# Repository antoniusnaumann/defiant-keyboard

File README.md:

# Defiant Keyboard
## Firmware
You can find the firmware here: https://github.com/antoniusnaumann/defiant-zmk

## Bill of Materials
(Diodes are not included, order PCBs with diodes assembled)

| Component      | Product                      | Quantity | Link                                                            |
|----------------|------------------------------|----------|-----------------------------------------------------------------|
| Hotswap Socket | Gateron KS-33 Hotswap Socket | 44       | https://www.aliexpress.com/item/1005006042596309.html           |
| LiPo Battery   | LP401230, 3,7V, ~100mAh      |  2       | https://eckstein-shop.de/LiPo-Akku-Lithium-Ion-Polymer-Batterie-37V-105mAh-mit-JST-PHR-2-Stecker-LP401230 |
| Connector      | JST-PH 2.0 2 Pin Angled      |  2       | https://www.digikey.de/de/products/detail/jst-sales-america-inc/S2B-PH-K-S/926626 | 
| Controller     | Seeedstudio XIAO nrf52840    |  2       | https://www.seeedstudio.com/Seeed-XIAO-BLE-nRF52840-p-5201.html | 
| EVA Foam*      | 2mm and 1mm                  |  1 each  | |

*EVA foam is optional and needs to be cut with a laser cutter. See SVG files in case/

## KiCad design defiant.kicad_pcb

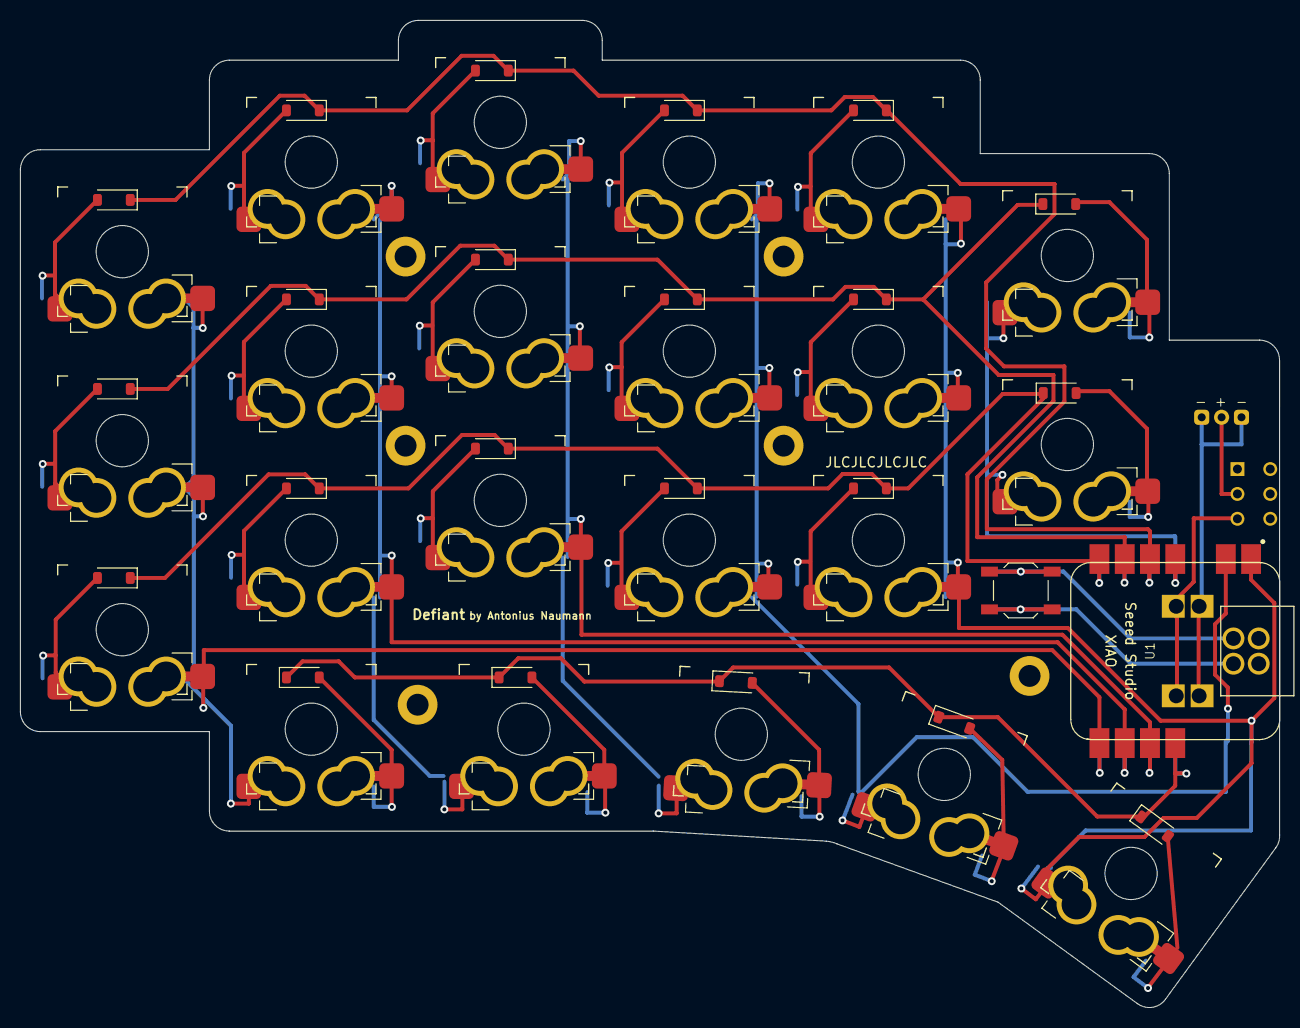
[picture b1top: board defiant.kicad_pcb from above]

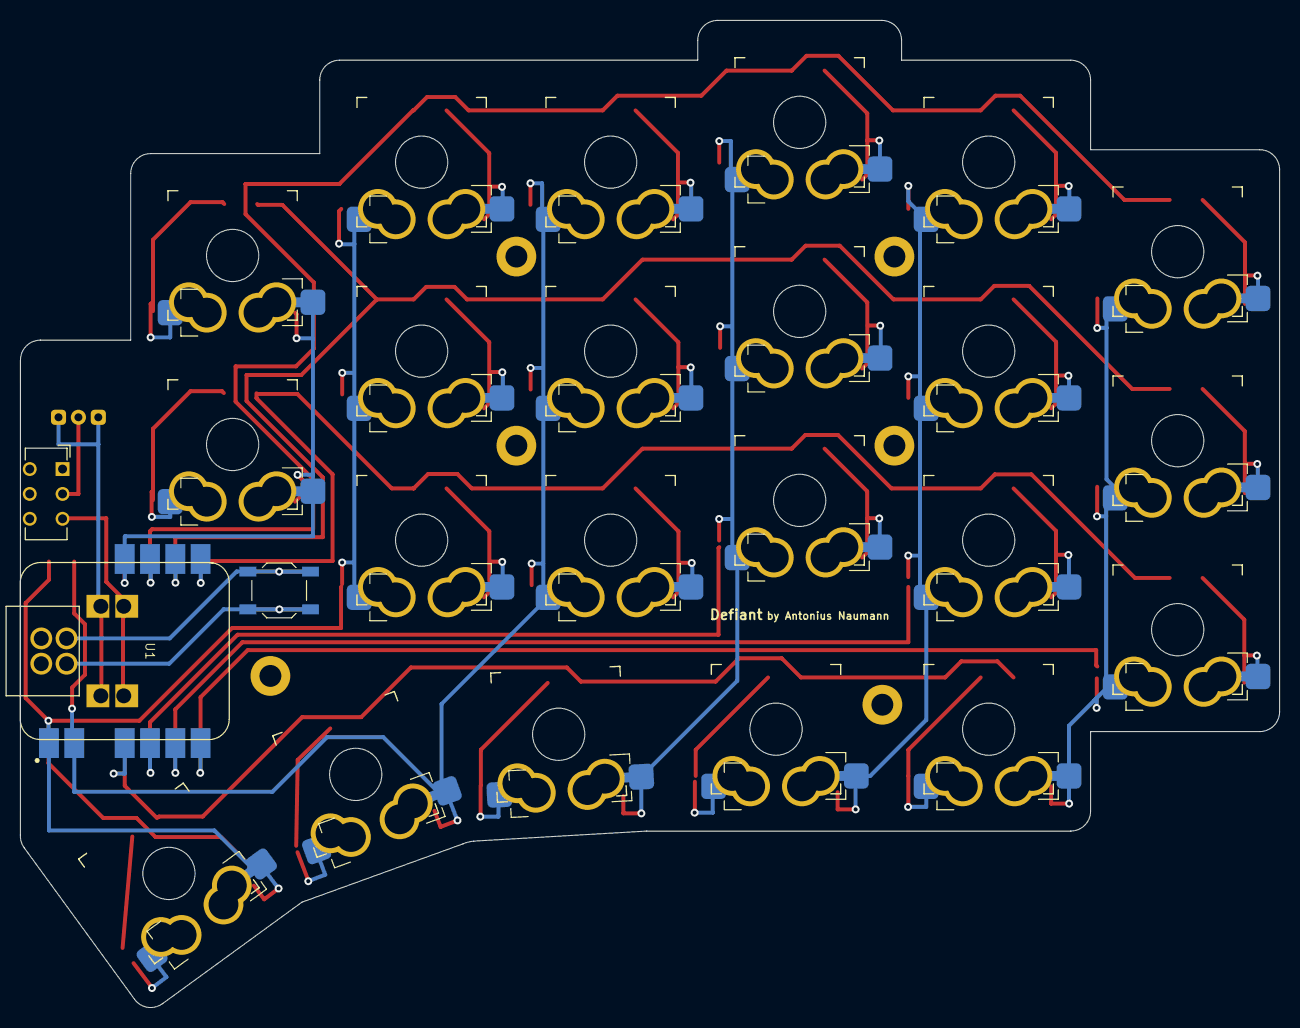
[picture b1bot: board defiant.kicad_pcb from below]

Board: 2 copper layers, 126.6 x 99.2 mm, 49 parts (17 on the bottom side), 37 nets.

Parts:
C0R1, C0R2, C0R3, C1R1, C1R2, C1R3, C2R1, C2R2, C2R3, C3R1, C3R2, C3R3, C4R1, C4R2, C4R3, C5R2, C5R3: SW_PUSH; SW_Gateron_LowProfile_HotSwap_PTH_Reversible
D1, D2, D3, D4, D5, D6, D7, D8, D9, D10, D11, D12, D13, D14, D15, D16, D17, D18, D19, D20, D22, D23: D; D_SOD-123
J1: Conn_01x02_Pin; Lipo Connector
SW1, SW2: SW_Push; SW_SPST_TL3342
SW3: SW_DP3T; SW_CuK_JS202011AQN_DPDT_Angled
T0, T1, T2, T3, T4: SW_PUSH; SW_Gateron_LowProfile_HotSwap_PTH_Reversible
U1: Seeed Studio XIAO BLE; XIAO-nRF52840-Sense-14P-2.54-21X17.8MM_Reduced_Pins

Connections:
unnamed: C0R1.2, D1.2 (A)
unnamed: C0R2.2, D2.2 (A)
unnamed: C0R3.2, D3.2 (A)
unnamed: D4.2 (A), T0.2
unnamed: C1R1.2, D5.2 (A)
unnamed: C1R2.2, D6.2 (A)
unnamed: C1R3.2, D7.2 (A)
unnamed: D8.2 (A), T1.2
unnamed: C2R1.2, D9.2 (A)
unnamed: C2R2.2, D10.2 (A)
unnamed: C2R3.2, D11.2 (A)
unnamed: D12.2 (A), T2.2
unnamed: C3R1.2, D13.2 (A)
unnamed: C3R2.2, D14.2 (A)
unnamed: C3R3.2, D15.2 (A)
unnamed: D16.2 (A), T3.2
unnamed: C4R1.2, D17.2 (A)
unnamed: C4R2.2, D18.2 (A)
unnamed: C4R3.2, D19.2 (A)
unnamed: D20.2 (A), T4.2
unnamed: C5R2.2, D22.2 (A)
unnamed: C5R3.2, D23.2 (A)
unnamed: J1.1, U1.21 (BAT-)
unnamed: J1.2, SW3.2
unnamed: SW1.2, SW2.2, U1.20 (GND)
unnamed: SW3.3, U1.22 (BAT+)
unnamed: SW1.1, SW2.1, U1.19 (RESET)
col0: C0R1.1, C0R2.1, C0R3.1, T0.1, U1.8 (PB09_A7_D7_RX)
col1: C1R1.1, C1R2.1, C1R3.1, T1.1, U1.9 (PA7_A8_D8_SCK)
col2: C2R1.1, C2R2.1, C2R3.1, T2.1, U1.10 (PA5_A9_D9_MISO)
col3: C3R1.1, C3R2.1, C3R3.1, T3.1, U1.2 (PA4_A1_D1)
col4: C4R1.1, C4R2.1, C4R3.1, T4.1, U1.1 (PA02_A0_D0)
col5: C5R2.1, C5R3.1, U1.4 (PA11_A3_D3)
row0: D1.1 (K), D5.1 (K), D9.1 (K), D13.1 (K), D17.1 (K), U1.5 (PA8_A4_D4_SDA)
row1: D2.1 (K), D6.1 (K), D10.1 (K), D14.1 (K), D18.1 (K), D22.1 (K), U1.6 (PA9_A5_D5_SCL)
row2: D3.1 (K), D7.1 (K), D11.1 (K), D15.1 (K), D19.1 (K), D23.1 (K), U1.7 (PB08_A6_D6_TX)
row3: D4.1 (K), D8.1 (K), D12.1 (K), D16.1 (K), D20.1 (K), U1.11 (PA6_A10_D10_MOSI)

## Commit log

2024-02-17 Init repository
2024-02-17 Change thumb pad to regular keys
2024-02-17 Move home thumb key up
2024-02-18 Update footprints
2024-02-18 Add power switch and reset button
2024-02-18 Create JLCPCB production files
2024-02-18 Add defiant plate files
2024-02-19 Add footprint for laser cut plate with 0.1mm kerf correction
2024-02-19 Add exact keycap boundary to switch footprint
2024-02-19 Change thumb keycap bounds to 1.25u and 1.75u
2024-02-20 Experimental: Tighten thumb key placing
2024-02-29 Move pinky column down by 1mm
2024-03-07 Replace XIAO BLE handsolder footprint with SMD solder footprint
2024-03-14 Change pcb lane width to 0.4mm
2024-03-14 Move vias out of pads
2024-03-15 Update production files
2024-04-21 Add exported case models
2024-04-21 Add svgs for cutting bottom plate foam
2024-04-21 Add svg for second layer bottom foam
2024-04-28 Update silk screen
2024-05-15 Add custom thumb key models
2024-05-15 Fix power switch wiring
2024-09-23 Update thumb keycaps to not collide with standard keycaps
2024-09-24 Add version of bottom plate with reset button hole
2024-09-28 Update thumb keycaps with signifiers
2024-10-01 Update bottom plates
2024-10-01 Add v2 case with integrated plate
2024-10-04 Add reset pin holes to bottom plates
2025-01-15 Add BOM
2025-01-25 Add bottom plate version for 3.5mm high switch
2025-01-27 Add plate foam
2025-01-27 Foam with holding tabs
